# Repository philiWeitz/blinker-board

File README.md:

# Eagle project for a simple Attiny with gyroscope support

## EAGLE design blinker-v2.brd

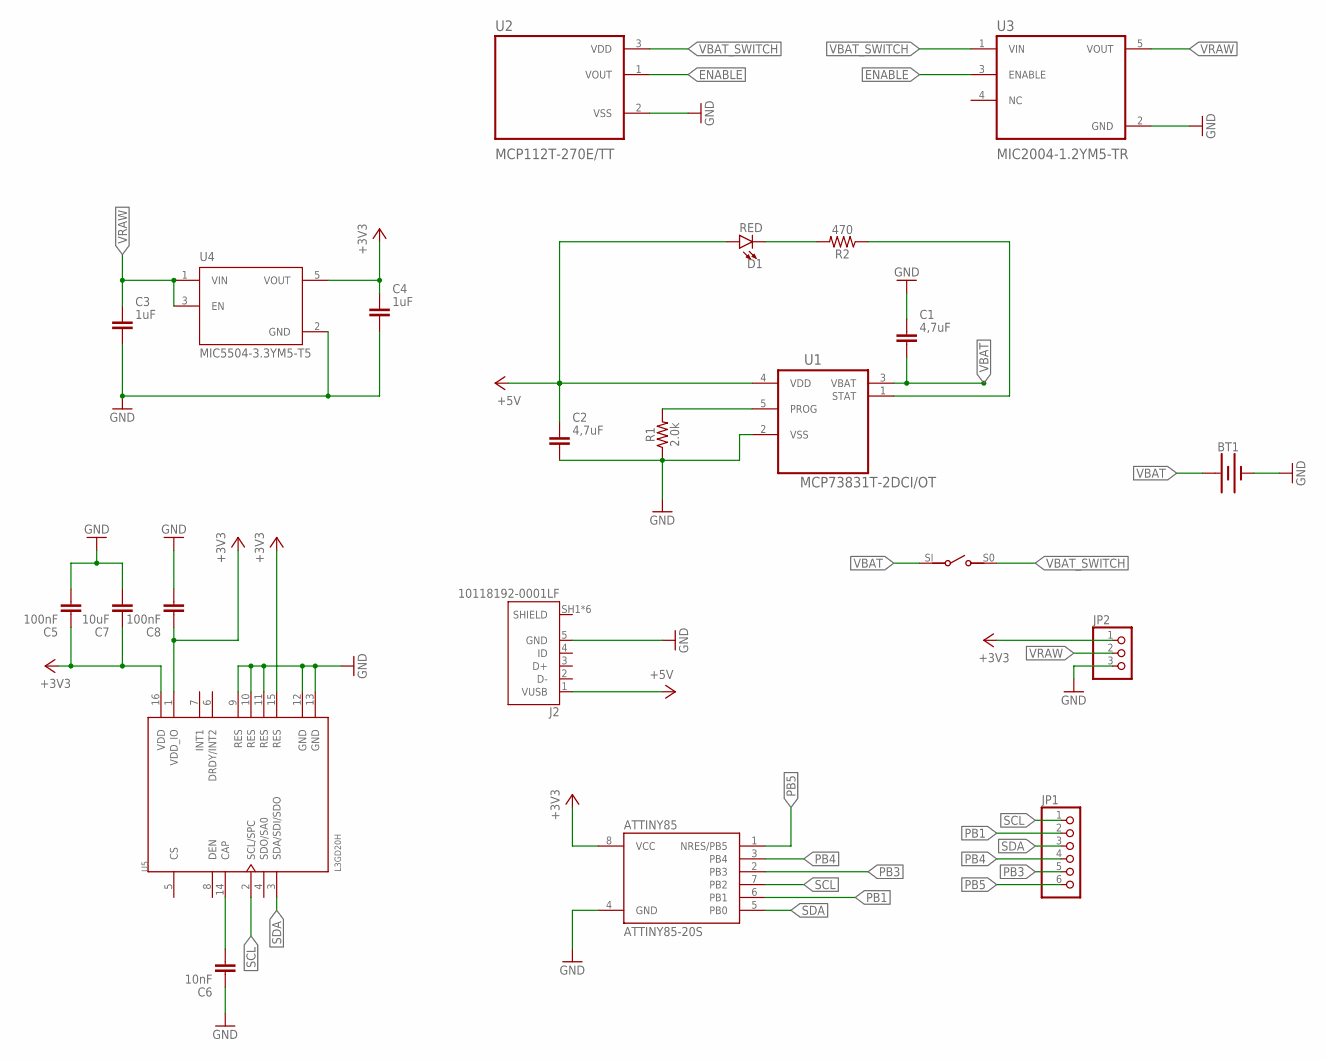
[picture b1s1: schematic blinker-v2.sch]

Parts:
ATTINY85: ATTINY85-20S; SOIC8_EIAJ_208MIL
BT1: BATTERY-20MM_SMD; BATTCON_20MM
C1, C2: 4,7uF; CAPC3216X135; DIGIKEY_PART_NR 1276-3107-1-ND
C3, C4: 1uF; CAPC3216X135
C5, C8: 100nF; CAPC3216X135
C6: 10nF; CAPC3216X135
C7: 10uF; CAPC3216X135
D1: RED; LED-0603; DIGIKEY_PART_NR 732-4978-1-ND
J2: 10118192-0001LF; AMPHENOL_10118192-0001LF
JP1: PINHD-1X6; 1X06
JP2: PINHD-1X3; 1X03
R1: 2.0k; 0603; DIGIKEY_PART_NR RMCF0201FT2K00CT-ND
R2: 470; 0603; DIGIKEY_PART_NR YAG2689CT-ND
U1: MCP73831T-2DCI/OT; SOT95P270X145-5N
U2: MCP112T-270E/TT; SOT95P237X112-3N
U3: MIC2004-1.2YM5-TR; SOT95P280X145-5N
U4: MIC5504-3.3YM5-T5; SOT95P280X145-5N
U5: L3GD20H; LGA16R50P7X5_300X300X100
U$1: CHS-01TASMD; CHS-01TA

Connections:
+3V3: ATTINY85.8 (VCC), C4.1, C5.1, C7.1, C8.1, JP2.1, U4.5 (VOUT), U5.1 (VDD_IO), U5.15 (RES), U5.16 (VDD)
+5V: C2.1, D1.A, J2.1 (VUSB), U1.4 (VDD)
ENABLE: U2.1 (VOUT), U3.3 (ENABLE)
GND: ATTINY85.4 (GND), BT1.2 (-), C1.1, C2.2, C3.2, C4.2, C5.2, C6.1, C7.2, C8.2, J2.5 (GND), JP2.3, R1.1, U1.2 (VSS), U2.2 (VSS), U3.2 (GND), U4.2 (GND), U5.9 (RES), U5.10 (RES), U5.11 (RES), U5.12 (GND), U5.13 (GND)
unnamed: R1.2, U1.5 (PROG)
unnamed: C6.2, U5.14 (CAP)
unnamed: D1.C, R2.2
unnamed: R2.1, U1.1 (STAT)
PB1: ATTINY85.6 (PB1), JP1.2
PB3: ATTINY85.2 (PB3), JP1.5
PB4: ATTINY85.3 (PB4), JP1.4
PB5: ATTINY85.1 (NRES/PB5), JP1.6
SCL: ATTINY85.7 (PB2), JP1.1, U5.2 (SCL/SPC)
SDA: ATTINY85.5 (PB0), JP1.3, U5.3 (SDA/SDI/SDO)
VBAT: BT1.1 (+), C1.2, U1.3 (VBAT), U$1.SI (S!)
VBAT_SWITCH: U2.3 (VDD), U3.1 (VIN), U$1.S0 (SO)
VRAW: C3.1, JP2.2, U3.5 (VOUT), U4.1 (VIN), U4.3 (EN)

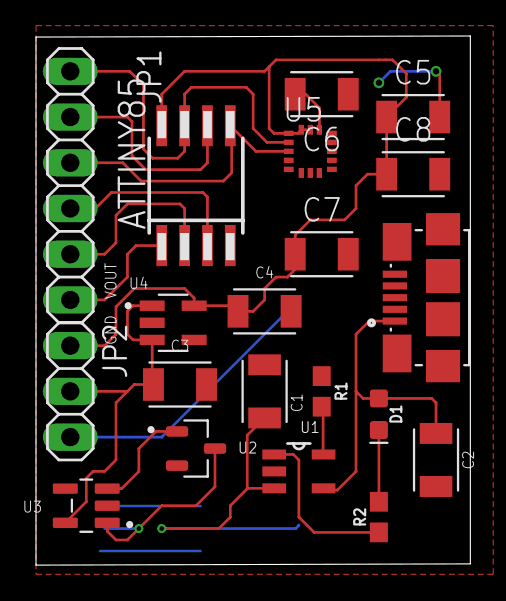
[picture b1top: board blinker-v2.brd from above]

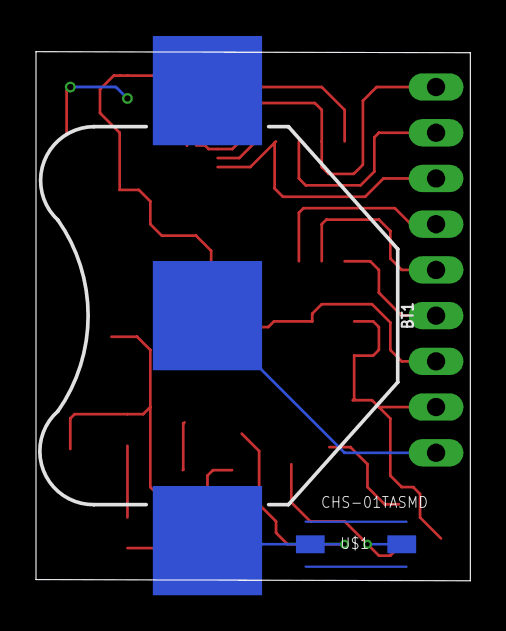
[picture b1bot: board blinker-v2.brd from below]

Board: 2 copper layers, 24.1 x 29.4 mm, 22 parts (2 on the bottom side), 17 nets.

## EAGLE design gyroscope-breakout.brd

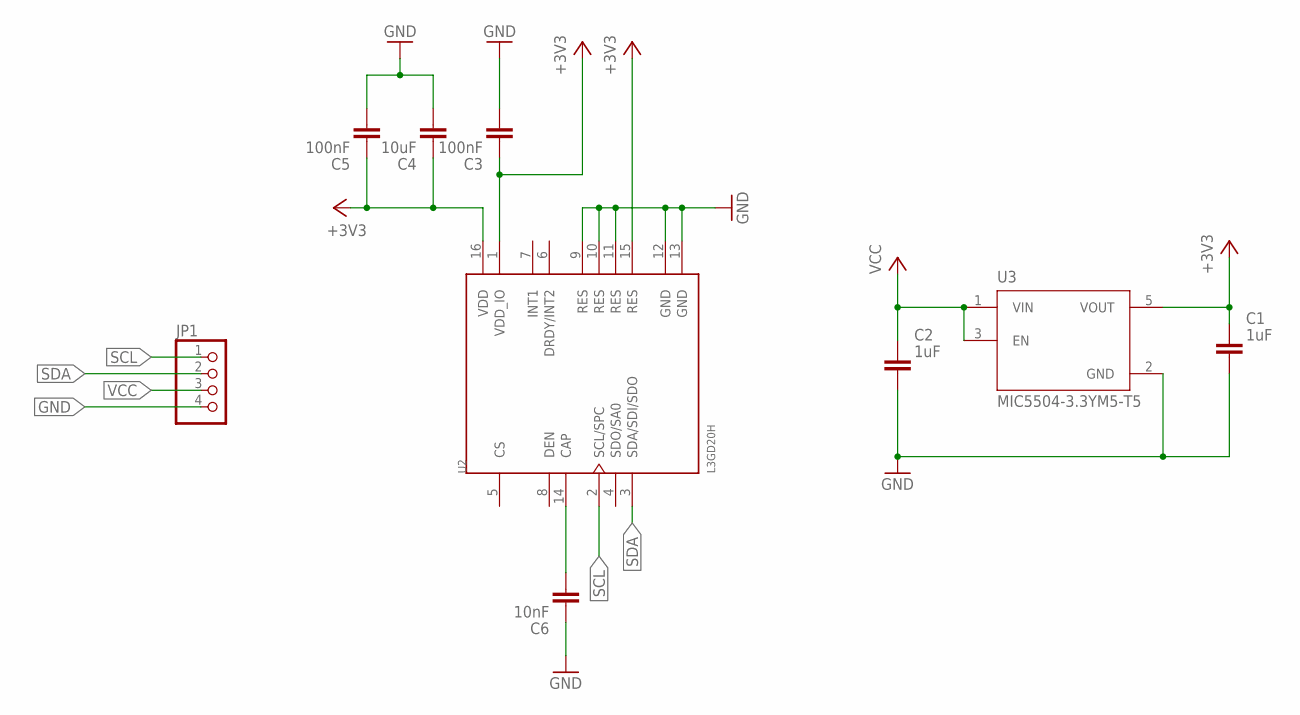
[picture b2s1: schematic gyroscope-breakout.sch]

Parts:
C1, C2: 1uF; CAPC3216X135
C3, C5: 100nF; CAPC3216X135
C4: 10uF; CAPC3216X135
C6: 10nF; CAPC3216X135
JP1: PINHD-1X4; 1X04
U2: L3GD20H; LGA16R50P7X5_300X300X100
U3: MIC5504-3.3YM5-T5; SOT95P280X145-5N

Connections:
+3V3: C1.1, C3.1, C4.1, C5.1, U2.1 (VDD_IO), U2.15 (RES), U2.16 (VDD), U3.5 (VOUT)
GND: C1.2, C2.2, C3.2, C4.2, C5.2, C6.1, JP1.4, U2.9 (RES), U2.10 (RES), U2.11 (RES), U2.12 (GND), U2.13 (GND), U3.2 (GND)
unnamed: C6.2, U2.14 (CAP)
SCL: JP1.1, U2.2 (SCL/SPC)
SDA: JP1.2, U2.3 (SDA/SDI/SDO)
VCC: C2.1, JP1.3, U3.1 (VIN), U3.3 (EN)

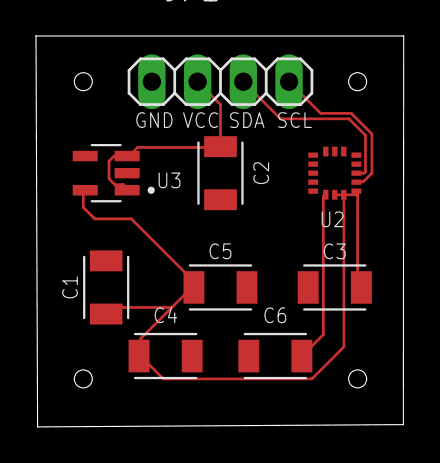
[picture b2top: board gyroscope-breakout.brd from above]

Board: 2 copper layers, 20.4 x 21.7 mm, 9 parts (0 on the bottom side), 6 nets.

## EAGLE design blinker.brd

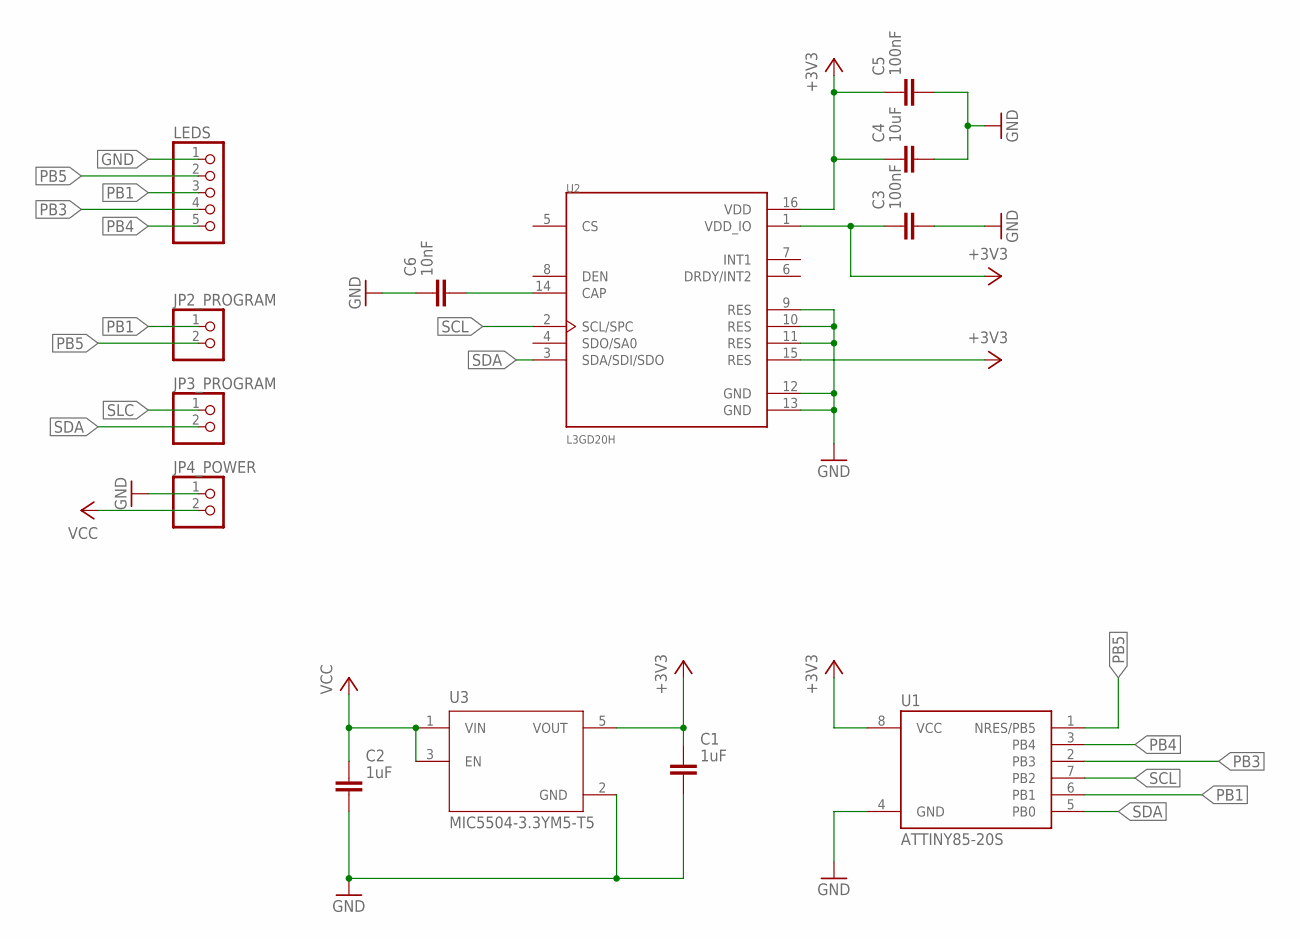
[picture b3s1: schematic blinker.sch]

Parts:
C1, C2: 1uF; CAPC3216X135
C3, C5: 100nF; CAPC3216X135
C4: 10uF; CAPC3216X135
C6: 10nF; CAPC3216X135
JP2_PROGRAM, JP3_PROGRAM, JP4_POWER: PINHD-1X2/90; 1X02/90
LEDS: PINHD-1X5/90; 1X05/90
U1: ATTINY85-20S; SOIC8_EIAJ_208MIL
U2: L3GD20H; LGA16R50P7X5_300X300X100
U3: MIC5504-3.3YM5-T5; SOT95P280X145-5N

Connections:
+3V3: C1.1, C3.1, C4.1, C5.1, U1.8 (VCC), U2.1 (VDD_IO), U2.15 (RES), U2.16 (VDD), U3.5 (VOUT)
GND: C1.2, C2.2, C3.2, C4.2, C5.2, C6.1, JP4_POWER.1, LEDS.1, U1.4 (GND), U2.9 (RES), U2.10 (RES), U2.11 (RES), U2.12 (GND), U2.13 (GND), U3.2 (GND)
unnamed: C6.2, U2.14 (CAP)
PB1: JP2_PROGRAM.1, LEDS.3, U1.6 (PB1)
PB3: LEDS.4, U1.2 (PB3)
PB4: LEDS.5, U1.3 (PB4)
PB5: JP2_PROGRAM.2, LEDS.2, U1.1 (NRES/PB5)
SCL: U1.7 (PB2), U2.2 (SCL/SPC)
SDA: JP3_PROGRAM.2, U1.5 (PB0), U2.3 (SDA/SDI/SDO)
SLC: JP3_PROGRAM.1
VCC: C2.1, JP4_POWER.2, U3.1 (VIN), U3.3 (EN)

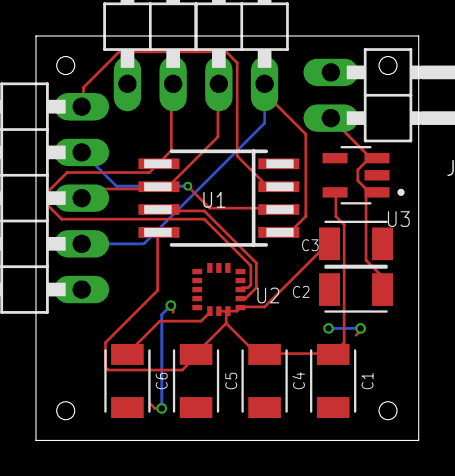
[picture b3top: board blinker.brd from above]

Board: 2 copper layers, 21.3 x 22.5 mm, 13 parts (0 on the bottom side), 10 nets.

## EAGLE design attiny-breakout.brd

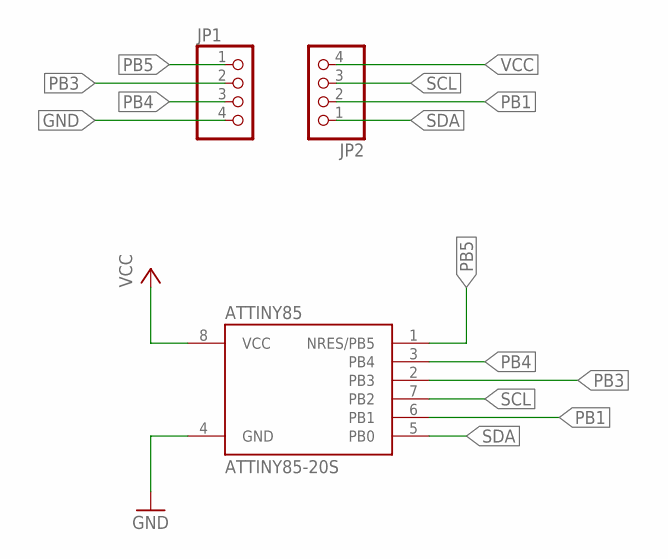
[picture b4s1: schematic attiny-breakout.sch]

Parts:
ATTINY85: ATTINY85-20S; SOIC8_EIAJ_208MIL
JP1, JP2: PINHD-1X4; 1X04

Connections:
GND: ATTINY85.4 (GND), JP1.4
PB1: ATTINY85.6 (PB1), JP2.2
PB3: ATTINY85.2 (PB3), JP1.2
PB4: ATTINY85.3 (PB4), JP1.3
PB5: ATTINY85.1 (NRES/PB5), JP1.1
SCL: ATTINY85.7 (PB2), JP2.3
SDA: ATTINY85.5 (PB0), JP2.1
VCC: ATTINY85.8 (VCC), JP2.4

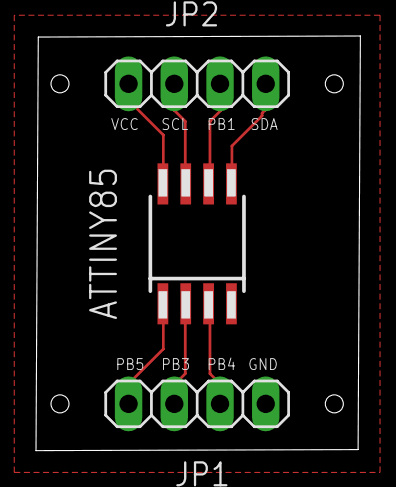
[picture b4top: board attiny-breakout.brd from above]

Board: 2 copper layers, 18.0 x 23.0 mm, 3 parts (0 on the bottom side), 8 nets.

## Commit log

2020-08-19 add gyro and attiny breakout boards
2020-08-19 fix gyro connections
2020-08-20 add board images
2020-08-24 add lipo charger circuit
2020-08-25 add under charge protection
2020-08-26 add on / off switch to charger
2020-08-27 finalize battery charger
2020-09-01 all in one board

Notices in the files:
parts and their libraries:
SparkFun-LED: Licensing: Creative Commons ShareAlike 4.0 International - https://creativecommons.org/licenses/by-sa/4.0
